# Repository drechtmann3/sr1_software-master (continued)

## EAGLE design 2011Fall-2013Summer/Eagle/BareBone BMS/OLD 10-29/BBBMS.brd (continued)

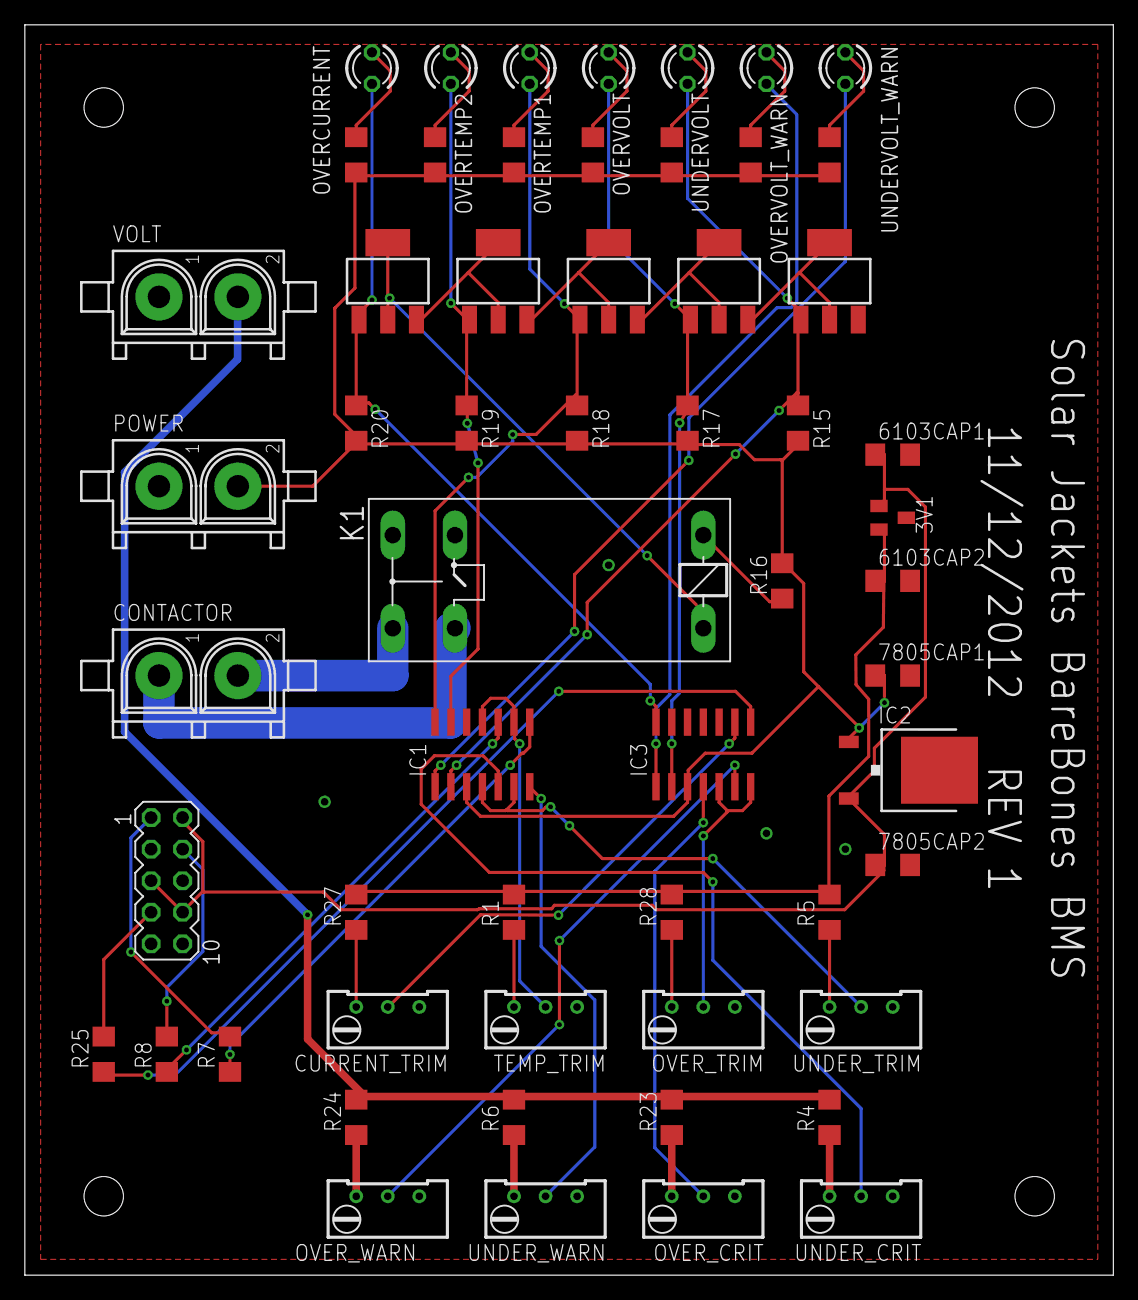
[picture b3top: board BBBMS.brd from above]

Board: 2 copper layers, 87.6 x 100.6 mm, 57 parts (0 on the bottom side), 49 nets.

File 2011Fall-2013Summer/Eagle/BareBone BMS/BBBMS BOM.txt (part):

Partlist exported from C:/Users/Reid Kersey/Documents/School/Solar Jackets/SubVersion/Eagle/BareBone BMS/BBBMS.sch at 11/14/2012 2:11:55 AM

Part            Value               Device              Package  Description                                                    MF                   MPN OC_FARNELL OC_NEWARK
3V1             MAX6103             MAX6103             SOT23                                                                                                                
6103CAP1        1uF                 C-USC0402           C0402    CAPACITOR, American symbol                                                                                  
6103CAP2        1uF                 C-USC0402           C0402    CAPACITOR, American symbol                                                                                  
7805CAP1        1uF                 C-USC0402           C0402    CAPACITOR, American symbol                                                                                  
7805CAP2        1uF                 C-USC0402           C0402    CAPACITOR, American symbol                                                                                  
CONTACTOR       350428-1            350428-1            350428-1 Universal MATE-N-LOK .250" Centerline, 600 V, 19 - 36 A max                                                 
CURRENT_TRIM    1k                  R-TRIMM64W          RTRIM64W Trimm resistor                                                                                              
IC1             LM339D              LM339D              SO14     Low Power Low Offset Voltage Quad Comparators                                                               
IC2             7805DT              7805DT              TO252    Positive VOLTAGE REGULATOR                                                                                  
IC3             LM339D              LM339D              SO14     Low Power Low Offset Voltage Quad Comparators                                                               
K1              G2REA               G2REA               G2REA    RELAY                                                                                   unknown    unknown  
OVERCURRENT     TLLG4400            TLLG4400            LED3MM   Low Current (2mA) LED 3 mm Tinted Diffused Package color GREEN VISHAY SEMICONDUCTOR     1612435             
OVERCURRENT_FET N-HEXFET-2D_SOT232- N-HEXFET-2D_SOT232- SOT223   HEXFET® Power MOSFET 2 Drain connects                                                                       
OVERTEMP1       TLLG4400            TLLG4400            LED3MM   Low Current (2mA) LED 3 mm Tinted Diffused Package color GREEN VISHAY SEMICONDUCTOR     1612435             
OVERTEMP1_FET   N-HEXFET-2D_SOT232- N-HEXFET-2D_SOT232- SOT223   HEXFET® Power MOSFET 2 Drain connects                                                                       
OVERTEMP2       TLLG4400            TLLG4400            LED3MM   Low Current (2mA) LED 3 mm Tinted Diffused Package color GREEN VISHAY SEMICONDUCTOR     1612435             
OVERTEMP2_FET   N-HEXFET-2D_SOT232- N-HEXFET-2D_SOT232- SOT223   HEXFET® Power MOSFET 2 Drain connects                                                                       
OVERVOLT        TLLG4400            TLLG4400            LED3MM   Low Current (2mA) LED 3 mm Tinted Diffused Package color GREEN VISHAY SEMICONDUCTOR     1612435             
OVERVOLT_FET    N-HEXFET-2D_SOT232- N-HEXFET-2D_SOT232- SOT223   HEXFET® Power MOSFET 2 Drain connects                                                                       
OVERVOLT_WARN   TLLG4400            TLLG4400            LED3MM   Low Current (2mA) LED 3 mm Tinted Diffused Package color GREEN VISHAY SEMICONDUCTOR     1612435             
OVER_CRIT       10k                 R-TRIMM64W          RTRIM64W Trimm resistor                                                                                              
OVER_TRIM       1k                  R-TRIMM64W          RTRIM64W Trimm resistor                                                                                              
OVER_WARN       10K                 R-TRIMM64W          RTRIM64W Trimm resistor                                                                                              
POWER           350428-1            350428-1            350428-1 Universal MATE-N-LOK .250" Centerline, 600 V, 19 - 36 A max                                                 
R1              100                 R-US_M1406          M1406    RESISTOR, American symbol                                                                                   
R4              100k                R-US_M1406          M1406    RESISTOR, American symbol                                                                                   
R5              100                 R-US_M1406          M1406    RESISTOR, American symbol                                                                                   
R6              100k                R-US_M1406          M1406    RESISTOR, American symbol                                                                                   
R7              100                 R-US_M1406          M1406    RESISTOR, American symbol                                                                                   
R8              100                 R-US_M1406          M1406    RESISTOR, American symbol                                                                                   
R9              1k                  R-US_M1406          M1406    RESISTOR, American symbol                                                                                   
R10             1k                  R-US_M1406          M1406    RESISTOR, American symbol                                                                                   
R13             1k                  R-US_M1406          M1406    RESISTOR, American symbol                                                                                   
R14             1k                  R-US_M1406          M1406    RESISTOR, American symbol                                                                                   
R15             1k                  R-US_M1406          M1406    RESISTOR, American symbol                                                                                   
R16             100                 R-US_M1406          M1406    RESISTOR, American symbol                                                                                   
R17             1k                  R-US_M1406          M1406    RESISTOR, American symbol                                                                                   
R18             1k                  R-US_M1406          M1406    RESISTOR, American symbol                                                                                   
R19             1k                  R-US_M1406          M1406    RESISTOR, American symbol                                                                                   
R20             1k                  R-US_M1406          M1406    RESISTOR, American symbol                                                                                   
R23             100k                R-US_M1406          M1406    RESISTOR, American symbol                                                                                   
R24             100k                R-US_M1406          M1406    RESISTOR, American symbol                                                                                   
R25             1k                  R-US_M1406          M1406    RESISTOR, American symbol                                                                                   
R27             100                 R-US_M1406          M1406    RESISTOR, American symbol                                                                                   
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
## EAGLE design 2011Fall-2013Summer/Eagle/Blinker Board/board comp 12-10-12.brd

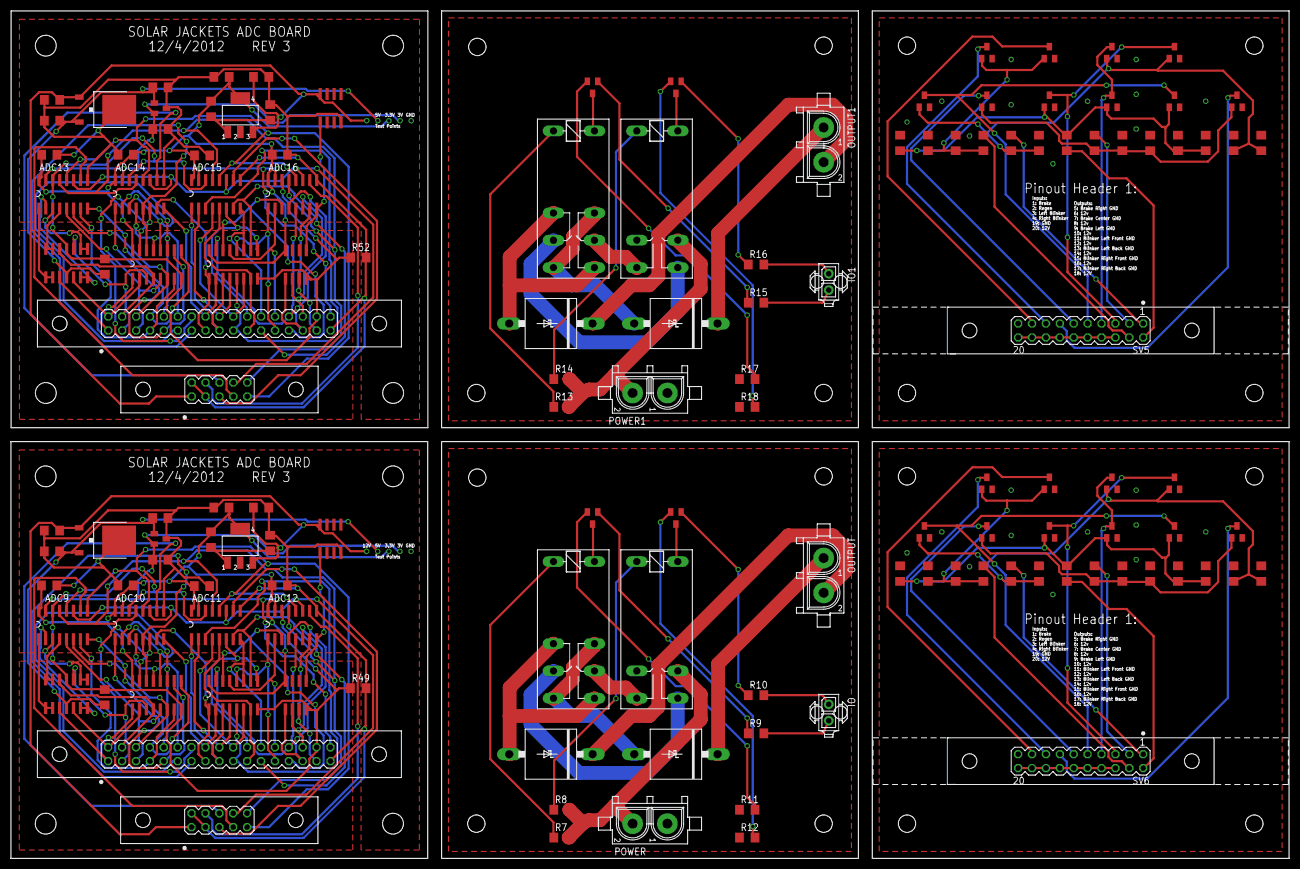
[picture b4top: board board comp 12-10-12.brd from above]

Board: 2 copper layers, 233.7 x 154.9 mm, 136 parts (0 on the bottom side), 170 nets.

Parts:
3V2, 3V3: MAX6103; SOT23
5V2, 5V3: LM7805TV; TO252
317CAP5, 317CAP7, 7805CAP6, 7805CAP8: .33uF; C1206
317CAP6, 317CAP8, 6103CAP5, 6103CAP6, 6103CAP7, 6103CAP8, 7805CAP5, 7805CAP7: 1uF; C1206
6484CAP3, 6484CAP4: .1uF; C1206
ADC9, ADC10, ADC11, ADC12, ADC13, ADC14, ADC15, ADC16: MCP-3008; SO16
ADC_CAP9, ADC_CAP10, ADC_CAP11, ADC_CAP12, ADC_CAP13, ADC_CAP14, ADC_CAP15, ADC_CAP16: .1uF; C1206
BLINKER-L1, BLINKER-L2, BLINKER-L3, BLINKER-L4: PMV56XN215; SOT23
BLINKER-R1, BLINKER-R2, BLINKER-R3, BLINKER-R4: PMV56XN215; SOT23
BRAKE-C1, BRAKE-C2, BRAKE-C3, BRAKE-C4: PMV56XN215; SOT23
BRAKE-L1, BRAKE-L2, BRAKE-L3, BRAKE-L4: PMV56XN215; SOT23
BRAKE-R1, BRAKE-R2, BRAKE-R3, BRAKE-R4: PMV56XN215; SOT23
D1, D2, D3, D4: 6A4; P6T15
IC3, IC4: LM317; SOT223
IO, IO1: 794681-2
K1, K3: G2R2
K2, K4: G2R2A
LMC6484_3, LMC6484_4: LMC6484; SO14
OUTPUT, OUTPUT1: 350428-1
POWER, POWER1: 350428-1
R7, R8, R9, R10, R13, R14, R15, R16, R19, R20, R21, R22, R23, R24, R25, R26, R27, R28, R29, R30, R31, R32, R33, R34, R35, R36, R37, R38, R39, R40, R41, R42, R43, R44, R45, R46: 1k; R1206
R11, R12, R17, R18, R49, R52: 0; R1206
R47, R50: 220; R1206
R48, R51: 361; R1206
SV5, SV6: AMPLATCH-20; MA10-2
SV7, SV9: MA17-2
SV8, SV10: MA05-2
T1, T2, T3, T4: PMV56XN; SOT23
U$9, U$10, U$13, U$14: SP720APP; SO16
U$11, U$15: SP721APP; SO-08
U$12, U$16: LM35; SO-08

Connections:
3.3V2: 317CAP6.1, ADC9.16, ADC10.16, ADC11.16, ADC12.16, ADC_CAP9.1, ADC_CAP10.1, ADC_CAP11.1, ADC_CAP12.1, IC3.4, R47.1, U$9.16, U$10.16, U$11.8
3.3V3: 317CAP8.1, ADC13.16, ADC14.16, ADC15.16, ADC16.16, ADC_CAP13.1, ADC_CAP14.1, ADC_CAP15.1, ADC_CAP16.1, IC4.4, R50.1, U$13.16, U$14.16, U$15.8
5V2: 3V2.1, 5V2.2, 6103CAP5.1, 6484CAP3.1, 7805CAP5.1, LMC6484_3.4
5V3: 3V3.1, 5V3.2, 6103CAP7.1, 6484CAP4.1, 7805CAP7.1, LMC6484_4.4
12V2: K2.P1, POWER.2, R7.2, R8.2
12V3: K4.P1, POWER1.2, R13.2, R14.2
12V4: SV5.6, SV5.8, SV5.10, SV5.12, SV5.14, SV5.16, SV5.18, SV5.20
12V5: SV6.6, SV6.8, SV6.10, SV6.12, SV6.14, SV6.16, SV6.18, SV6.20
12V6: 5V2.1, 317CAP5.1, 7805CAP6.1, IC3.3, SV8.1, U$12.8
12V7: 5V3.1, 317CAP7.1, 7805CAP8.1, IC4.3, SV10.1, U$16.8
A9: ADC9.1, LMC6484_3.1, LMC6484_3.2
A10: ADC9.2, LMC6484_3.6, LMC6484_3.7
A11: ADC9.3, LMC6484_3.8, LMC6484_3.9
A12: ADC9.4, LMC6484_3.13, LMC6484_3.14
A13: ADC13.1, LMC6484_4.1, LMC6484_4.2
A14: ADC13.2, LMC6484_4.6, LMC6484_4.7
A15: ADC13.3, LMC6484_4.8, LMC6484_4.9
A16: ADC13.4, LMC6484_4.13, LMC6484_4.14
AGND2: 6484CAP3.2, ADC9.14, ADC10.14, ADC11.14, ADC12.14, LMC6484_3.11, R49.1, SV7.32, U$9.8, U$10.8, U$11.4
AGND3: 6484CAP4.2, ADC13.14, ADC14.14, ADC15.14, ADC16.14, LMC6484_4.11, R52.1, SV9.32, U$13.8, U$14.8, U$15.4
BLINKER_L: BLINKER-L1.1, BLINKER-L2.1, R23.2, R24.2, R32.2
BLINKER_L1: BLINKER-L3.1, BLINKER-L4.1, R37.2, R38.2, R46.2
BLINKER_L_BACK_-: BLINKER-L2.3, SV5.13
BLINKER_L_BACK_-1: BLINKER-L4.3, SV6.13
BLINKER_L_FRONT_-: BLINKER-L1.3, SV5.11
BLINKER_L_FRONT_-1: BLINKER-L3.3, SV6.11
BLINKER_R: BLINKER-R1.1, BLINKER-R2.1, R25.2, R26.2, R29.1
BLINKER_R1: BLINKER-R3.1, BLINKER-R4.1, R39.2, R40.2, R43.1
BLINKER_R_BACK_-: BLINKER-R2.3, SV5.17
BLINKER_R_BACK_-1: BLINKER-R4.3, SV6.17
BLINKER_R_FRONT_-: BLINKER-R1.3, SV5.15
BLINKER_R_FRONT_-1: BLINKER-R3.3, SV6.15
BRAKE: BRAKE-C1.1, BRAKE-L1.1, BRAKE-R1.1, R19.2, R21.2, R27.2, R31.2
BRAKE1: BRAKE-C4.1, BRAKE-L4.1, BRAKE-R3.1, R33.2, R35.2, R41.2, R45.2
BRAKE_C_-: BRAKE-C1.3, BRAKE-C2.3, SV5.7
BRAKE_C_-1: BRAKE-C3.3, BRAKE-C4.3, SV6.7
BRAKE_L_-: BRAKE-L1.3, BRAKE-L2.3, SV5.9
BRAKE_L_-1: BRAKE-L3.3, BRAKE-L4.3, SV6.9
BRAKE_REGEN: BRAKE-C2.1, BRAKE-L2.1, BRAKE-R2.1, R20.2, R22.2, R28.2, R30.1
BRAKE_REGEN1: BRAKE-C3.1, BRAKE-L3.1, BRAKE-R4.1, R34.2, R36.2, R42.2, R44.1
BRAKE_R_-: BRAKE-R1.3, BRAKE-R2.3, SV5.5
BRAKE_R_-1: BRAKE-R3.3, BRAKE-R4.3, SV6.5
DIR: IO.2, R9.2
DIR1: IO1.2, R15.2
GND2: K2.P2, POWER.1, R11.1, R12.1
GND3: K4.P2, POWER1.1, R17.1, R18.1
GND4: BLINKER-L1.2, BLINKER-L2.2, BLINKER-R1.2, BLINKER-R2.2, BRAKE-C1.2, BRAKE-C2.2, BRAKE-L1.2, BRAKE-L2.2, BRAKE-R1.2, BRAKE-R2.2, R19.1, R20.1, R21.1, R22.1, R23.1, R24.1, R25.1, R26.1, R27.1, R28.1, SV5.19
GND5: BLINKER-L3.2, BLINKER-L4.2, BLINKER-R3.2, BLINKER-R4.2, BRAKE-C3.2, BRAKE-C4.2, BRAKE-L3.2, BRAKE-L4.2, BRAKE-R3.2, BRAKE-R4.2, R33.1, R34.1, R35.1, R36.1, R37.1, R38.1, R39.1, R40.1, R41.1, R42.1, SV6.19
GND6: 3V2.3, 5V2.3, 317CAP5.2, 317CAP6.2, 6103CAP5.2, 6103CAP6.2, 7805CAP5.2, 7805CAP6.2, ADC9.9, ADC10.9, ADC11.9, ADC12.9, ADC_CAP9.2, ADC_CAP10.2, ADC_CAP11.2, ADC_CAP12.2, R48.2, R49.2, SV7.33, SV8.2, SV8.3, U$12.4
GND7: 3V3.3, 5V3.3, 317CAP7.2, 317CAP8.2, 6103CAP7.2, 6103CAP8.2, 7805CAP7.2, 7805CAP8.2, ADC13.9, ADC14.9, ADC15.9, ADC16.9, ADC_CAP13.2, ADC_CAP14.2, ADC_CAP15.2, ADC_CAP16.2, R51.2, R52.2, SV9.33, SV10.2, SV10.3, U$16.4
IN65: LMC6484_3.3, SV7.1, U$9.1
IN66: LMC6484_3.5, SV7.2, U$9.2
IN67: LMC6484_3.10, SV7.3, U$9.3
IN68: LMC6484_3.12, SV7.4, U$9.4
IN69: ADC9.8, SV7.8, U$9.9
IN70: ADC9.7, SV7.7, U$9.7
IN71: ADC9.6, SV7.6, U$9.6
IN72: ADC9.5, SV7.5, U$9.5
IN73: ADC10.2, SV7.10, U$9.11
IN74: ADC10.1, SV7.9, U$9.10
IN75: ADC10.5, SV7.13, U$9.14
IN76: ADC10.6, SV7.14, U$9.15
IN77: ADC11.8, SV7.24, U$10.11
IN78: ADC11.7, SV7.23, U$10.10
IN79: ADC11.5, SV7.21, U$10.7
IN80: ADC11.6, SV7.22, U$10.9
IN81: ADC11.4, SV7.20, U$10.6
IN82: ADC11.3, SV7.19, U$10.5
IN83: ADC11.1, SV7.17, U$10.3
IN84: ADC11.2, SV7.18, U$10.4
IN85: ADC12.1, SV7.25, U$10.12
IN86: ADC12.2, SV7.26, U$10.13
IN87: ADC12.4, SV7.28, U$10.15
IN88: ADC12.3, SV7.27, U$10.14
IN89: ADC12.8, U$11.5, U$12.1
IN90: ADC12.7, SV7.31, U$11.3
IN91: ADC12.5, SV7.29, U$11.1
IN92: ADC12.6, SV7.30, U$11.2
IN93: ADC10.8, SV7.16, U$10.2
IN94: ADC10.7, SV7.15, U$10.1
IN95: ADC10.3, SV7.11, U$9.12
IN96: ADC10.4, SV7.12, U$9.13
IN97: LMC6484_4.3, SV9.1, U$13.1
IN98: LMC6484_4.5, SV9.2, U$13.2
IN99: LMC6484_4.10, SV9.3, U$13.3
IN100: LMC6484_4.12, SV9.4, U$13.4
IN101: ADC13.8, SV9.8, U$13.9
IN102: ADC13.7, SV9.7, U$13.7
IN103: ADC13.6, SV9.6, U$13.6
IN104: ADC13.5, SV9.5, U$13.5
IN105: ADC14.2, SV9.10, U$13.11
IN106: ADC14.1, SV9.9, U$13.10
IN107: ADC14.5, SV9.13, U$13.14
IN108: ADC14.6, SV9.14, U$13.15
IN109: ADC15.8, SV9.24, U$14.11
IN110: ADC15.7, SV9.23, U$14.10
IN111: ADC15.5, SV9.21, U$14.7
IN112: ADC15.6, SV9.22, U$14.9
IN113: ADC15.4, SV9.20, U$14.6
IN114: ADC15.3, SV9.19, U$14.5
IN115: ADC15.1, SV9.17, U$14.3
IN116: ADC15.2, SV9.18, U$14.4
IN117: ADC16.1, SV9.25, U$14.12
IN118: ADC16.2, SV9.26, U$14.13
IN119: ADC16.4, SV9.28, U$14.15
IN120: ADC16.3, SV9.27, U$14.14
IN121: ADC16.8, U$15.5, U$16.1
IN122: ADC16.7, SV9.31, U$15.3
IN123: ADC16.5, SV9.29, U$15.1
IN124: ADC16.6, SV9.30, U$15.2
IN125: ADC14.8, SV9.16, U$14.2
IN126: ADC14.7, SV9.15, U$14.1
IN127: ADC14.3, SV9.11, U$13.12
IN128: ADC14.4, SV9.12, U$13.13
MOTOR+: D2.C, OUTPUT.2
MOTOR+1: D4.C, OUTPUT1.2
MOTOR+_PRE: D2.A, K1.O2, K1.S1
MOTOR+_PRE1: D4.A, K3.O2, K3.S1
MOTOR-: D1.C, OUTPUT.1
MOTOR-1: D3.C, OUTPUT1.1
MOTOR-_PRE: D1.A, K1.O1, K1.S2
MOTOR-_PRE1: D3.A, K3.O1, K3.S2
unnamed: K1.P2, K2.S1
unnamed: K1.P1, K2.S2
unnamed: K1.1, R7.1
unnamed: K2.1, R8.1
unnamed: K1.2, T1.3
unnamed: K2.2, T2.3
unnamed: R10.1, T2.1
unnamed: R9.1, T1.1
unnamed: R11.2, T1.2
unnamed: R12.2, T2.2
unnamed: K3.P2, K4.S1
unnamed: K3.P1, K4.S2
unnamed: K3.1, R13.1
unnamed: K4.1, R14.1
unnamed: K3.2, T3.3
unnamed: K4.2, T4.3
unnamed: R16.1, T4.1
unnamed: R15.1, T3.1
unnamed: R17.2, T3.2
unnamed: R18.2, T4.2
unnamed: R30.2, SV5.2
unnamed: R29.2, SV5.4
unnamed: R31.1, SV5.1
unnamed: R32.1, SV5.3
unnamed: R44.2, SV6.2
unnamed: R43.2, SV6.4
unnamed: R45.1, SV6.1
unnamed: R46.1, SV6.3
unnamed: IC3.1, R47.2, R48.1
unnamed: IC4.1, R50.2, R51.1
ON: IO.1, R10.2
ON1: IO1.1, R16.2
SPI_CLK2: ADC9.13, ADC10.13, ADC11.13, ADC12.13, SV8.10
SPI_CLK3: ADC13.13, ADC14.13, ADC15.13, ADC16.13, SV10.10
SPI_CS9: ADC9.10, SV8.7
SPI_CS10: ADC10.10, SV8.6
SPI_CS11: ADC12.10, SV8.4
SPI_CS12: ADC11.10, SV8.5
SPI_CS13: ADC13.10, SV10.7
SPI_CS14: ADC14.10, SV10.6
SPI_CS15: ADC16.10, SV10.4
SPI_CS16: ADC15.10, SV10.5
SPI_DIN2: ADC9.11, ADC10.11, ADC11.11, ADC12.11, SV8.8
SPI_DIN3: ADC13.11, ADC14.11, ADC15.11, ADC16.11, SV10.8
SPI_DOUT2: ADC9.12, ADC10.12, ADC11.12, ADC12.12, SV8.9
SPI_DOUT3: ADC13.12, ADC14.12, ADC15.12, ADC16.12, SV10.9
VREF2: 3V2.2, 6103CAP6.1, ADC9.15, ADC10.15, ADC11.15, ADC12.15, SV7.34
VREF3: 3V3.2, 6103CAP8.1, ADC13.15, ADC14.15, ADC15.15, ADC16.15, SV9.34

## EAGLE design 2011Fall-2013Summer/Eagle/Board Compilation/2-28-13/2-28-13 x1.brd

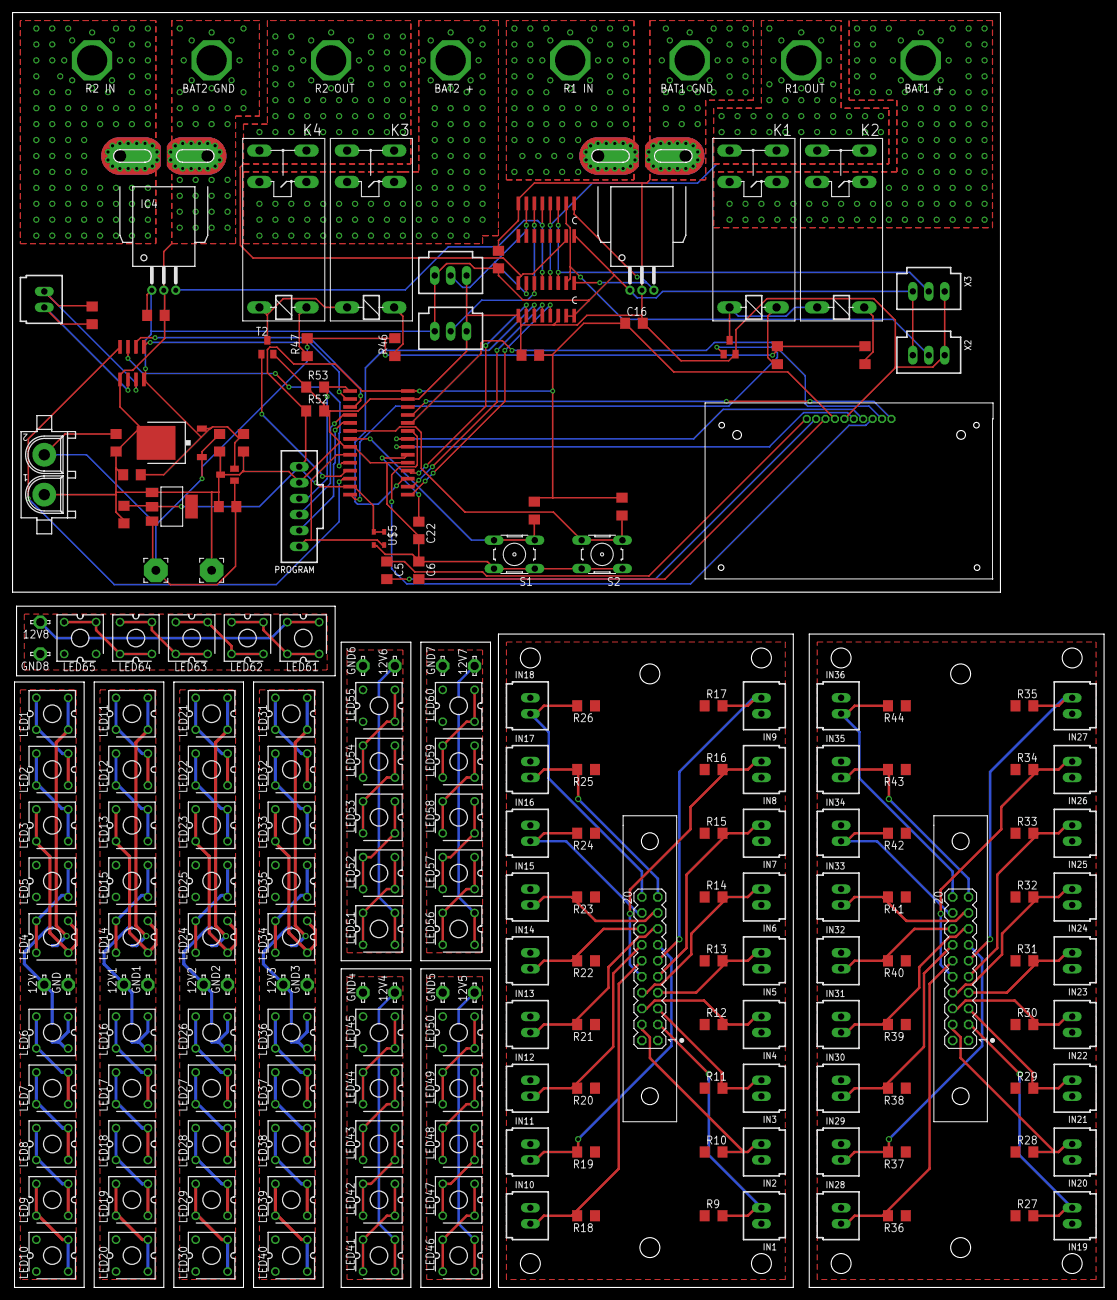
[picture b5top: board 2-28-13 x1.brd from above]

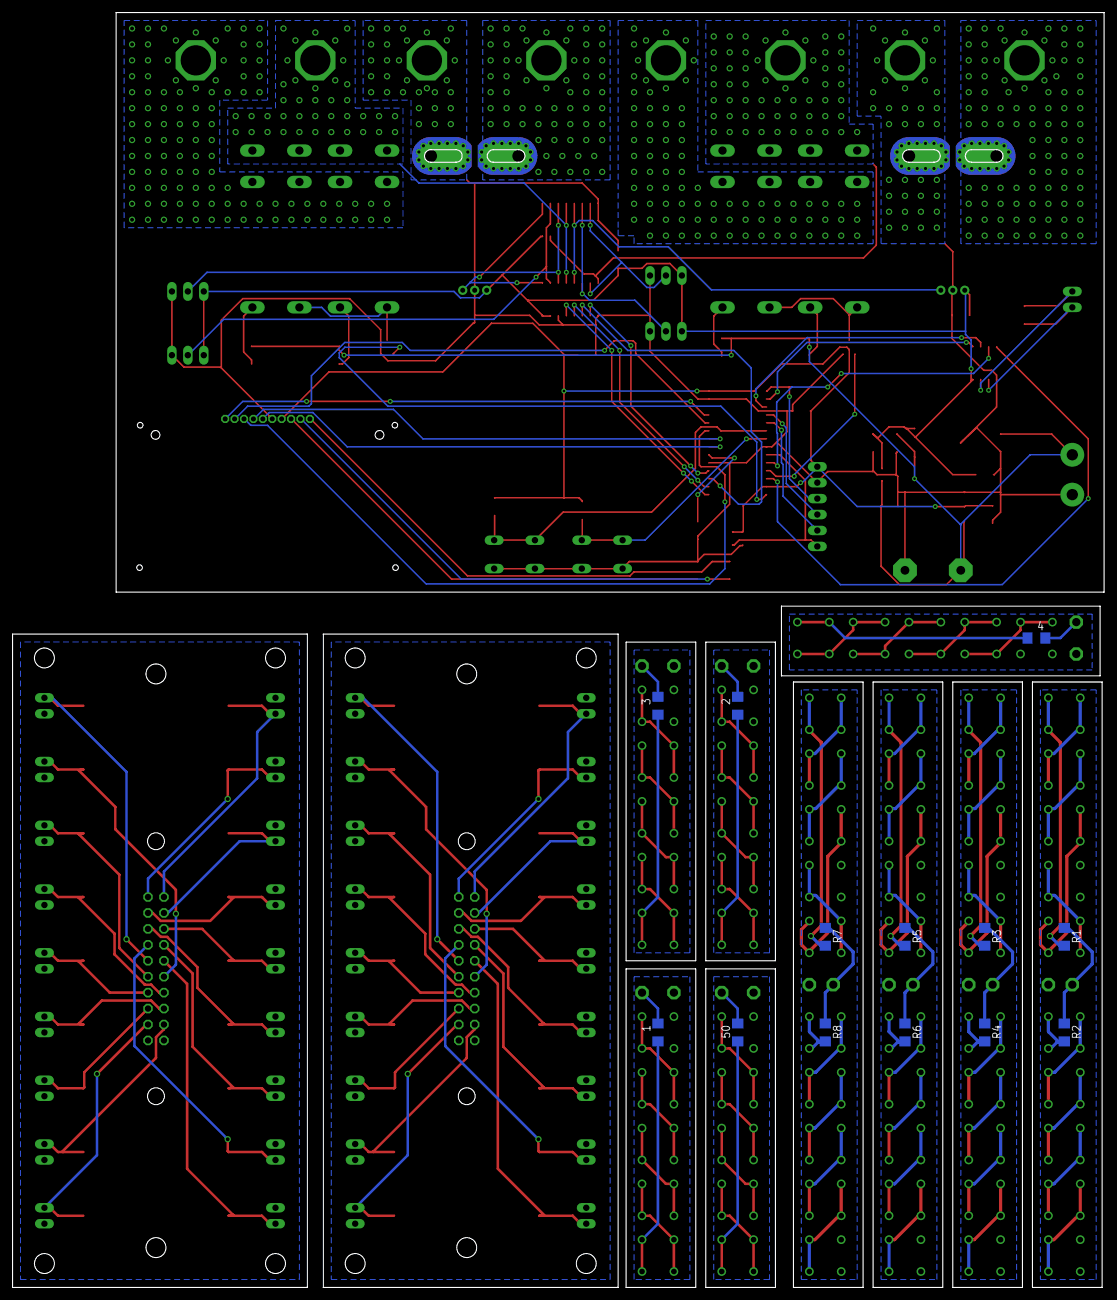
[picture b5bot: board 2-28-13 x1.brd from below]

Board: 2 copper layers, 174.0 x 203.2 mm, 228 parts (13 on the bottom side), 172 nets.

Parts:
1, 2, 3, 4, 50: RESISTORSMD1206; R1206
12V, 12V1, 12V2, 12V3, 12V4, 12V5, 12V6, 12V7, 12V8: LSP13
BAT+_1: BAT1 +; SOLDERPAD
BAT+_2: BAT2 +; SOLDERPAD
BAT-_1: BAT1 GND; SOLDERPAD
BAT-_2: BAT2 GND; SOLDERPAD
C1: .3uF; C1206
C2, C3, C4, C5, C6, C7, C8, C9, C10, C22: 1uF; C1206
C16, C48: .1uF; C1206
GND, GND1, GND2, GND3, GND4, GND5, GND6, GND7, GND8: LSP13
IC1: 7805DT; TO252
IC2, IC4: ACS758ECB-200B-PFF-T; CB-PFF
IC3: REG1117; SOT223
IN1, IN2, IN3, IN4, IN5, IN6, IN7, IN8, IN9, IN10, IN11, IN12, IN13, IN14, IN15, IN16, IN17, IN18, IN19, IN20, IN21, IN22, IN23, IN24, IN25, IN26, IN27, IN28, IN29, IN30, IN31, IN32, IN33, IN34, IN35, IN36: C-GRID-02-70543; 70543-02
J1: 350428-1
K1, K2, K3, K4: G2REA
LED1, LED11, LED21, LED31, LED41, LED46, LED51, LED56, LED61: LED1; CP41B
LED2, LED12, LED22, LED32, LED42, LED47, LED52, LED57, LED62: LED2; CP41B
LED3, LED13, LED23, LED33, LED43, LED48, LED53, LED58, LED63: LED3; CP41B
LED4, LED14, LED24, LED34, LED44, LED49, LED54, LED59, LED64: LED4; CP41B
LED5, LED15, LED25, LED35, LED45, LED50, LED55, LED60, LED65: LED5; CP41B
LED6, LED16, LED26, LED36: LED6; CP41B
LED7, LED17, LED27, LED37: LED7; CP41B
LED8, LED18, LED28, LED38: LED8; CP41B
LED9, LED19, LED29, LED39: LED9; CP41B
LED10, LED20, LED30, LED40: LED10; CP41B
PAD_12V: 12v; 3,81/1,4
PAD_GND: gnd; 3,81/1,4
PROGRAM: C-GRID-06-70543; 70543-06
R1, R2, R3, R4, R5, R6, R7, R8: 50; R1206
R9, R10, R11, R12, R13, R14, R15, R16, R17, R18, R19, R20, R21, R22, R23, R24, R25, R26, R27, R28, R29, R30, R31, R32, R33, R34, R35, R36, R37, R38, R39, R40, R41, R42, R43, R44, R45, R46, R47, R48, R49, R169: 1K; R1206
R50: 120; R1206
R52: 10k\; R1206
R53: 470; R1206
R_IN_1: R1 IN; SOLDERPAD
R_IN_2: R2 IN; SOLDERPAD
R_OUT_1: R1 OUT; SOLDERPAD
R_OUT_2: R2 OUT; SOLDERPAD
S1, S2: B3F-10XX
T1, T2: PMV56XN; SOT23
U$1, U$2: AMP_LATCH-20; MA10-2
U$3: MCP-3008; SO16
U$4: PIC24HJ128GP-202; SO28W
U$5: ASE
U$6: LCD_SCREEN
U$7: MAX6105; SOT23
U$8: SP720APP; SO16
U$9: MAX3440E; SO-08
X1: BAT2 TEMP 1; 70543-03
X2: BAT1 TEMP1; 70543-03
X3: BAT1 TEMP2; 70543-03
X4: BAT2 TEMP2; 70543-03
X5: rs-485; 70543-02

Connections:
3.3V: IN1.1, IN2.1, IN3.1, IN4.1, IN5.1, IN6.1, IN7.1, IN8.1, IN9.1, IN10.1, IN11.1, IN12.1, IN13.1, IN14.1, IN15.1, IN16.1, IN17.1, IN18.1, U$1.1
3.3V1: IN19.1, IN20.1, IN21.1, IN22.1, IN23.1, IN24.1, IN25.1, IN26.1, IN27.1, IN28.1, IN29.1, IN30.1, IN31.1, IN32.1, IN33.1, IN34.1, IN35.1, IN36.1, U$2.1
+3V3: C9.1, C16.1, C48.1, IC3.2, PROGRAM.6, R48.2, R49.1, R52.1, U$4.13, U$4.28, U$5.1, U$5.4, U$6.7
+5V: C3.2, C4.1, C7.1, C10.2, IC1.2, IC2.1, IC4.1, U$3.15, U$3.16, U$7.2, U$8.16, U$9.8, X1.3, X2.3, X3.3, X4.3
+12V: C1.1, C2.1, C8.1, IC1.1, IC3.3, J1.2, PAD_12V.1, R45.2, R46.2, R47.2, R169.2, U$7.1
CH0: IC2.3, U$3.1, U$8.1
CH1: U$3.2, U$8.2, X2.2
CH2: U$3.3, U$8.3, X3.2
CH3: K1.S, K1.S@, K2.S, K2.S@, R_OUT_1.P$1, U$3.4, U$8.4
CH4: IC4.3, U$3.5, U$8.5
CH5: U$3.6, U$8.6, X1.2
CH6: U$3.7, U$8.7, X4.2
CH7: K3.S, K3.S@, K4.S, K4.S@, R_OUT_2.P$1, U$3.8, U$8.15
GND: GND.MP, LED5.1, LED5.4, LED10.1, LED10.4
GND1: GND1.MP, LED15.1, LED15.4, LED20.1, LED20.4
GND2: GND2.MP, LED25.1, LED25.4, LED30.1, LED30.4
GND3: GND3.MP, LED35.1, LED35.4, LED40.1, LED40.4
GND4: GND4.MP, LED45.1, LED45.4
GND5: GND5.MP, LED50.1, LED50.4
GND6: GND6.MP, LED55.1, LED55.4
GND7: GND7.MP, LED60.1, LED60.4
GND8: GND8.MP, LED65.1, LED65.4
GND9: R9.1, R10.1, R11.1, R12.1, R13.1, R14.1, R15.1, R16.1, R17.1, R18.1, R19.1, R20.1, R21.1, R22.1, R23.1, R24.1, R25.1, R26.1, U$1.2
GND10: R27.1, R28.1, R29.1, R30.1, R31.1, R32.1, R33.1, R34.1, R35.1, R36.1, R37.1, R38.1, R39.1, R40.1, R41.1, R42.1, R43.1, R44.1, U$2.2
GND11: BAT-_1.P$1, BAT-_2.P$1, C1.2, C2.2, C3.1, C4.2, C6.1, C7.2, C8.2, C9.2, C10.1, C16.2, C22.2, C48.2, IC1.3, IC2.2, IC2.IP+, IC2.IP+@2, IC2.IP+@3, IC2.IP+@4, IC2.IP+@5, IC2.IP+@6, IC2.IP+@7, IC2.IP+@8, IC2.IP+@9, IC2.IP+@10, IC2.IP+@11, IC2.IP+@12, IC2.IP+@13, IC2.IP+@14, IC2.IP+@15, IC2.IP+@16, IC2.IP+@17, IC3.1, IC4.2, IC4.IP+, IC4.IP+@2, IC4.IP+@3, IC4.IP+@4, IC4.IP+@5, IC4.IP+@6, IC4.IP+@7, IC4.IP+@8, IC4.IP+@9, IC4.IP+@10, IC4.IP+@11, IC4.IP+@12, IC4.IP+@13, IC4.IP+@14, IC4.IP+@15, IC4.IP+@16, IC4.IP+@17, J1.1, PAD_GND.1, PROGRAM.5, R52.2, R53.1, S1.1, S1.2, S2.1, S2.2, T1.2, T2.2, U$3.9, U$3.14, U$4.8, U$4.19, U$4.27, U$5.2, U$6.6, U$7.3, U$8.8, U$9.5, X1.1, X2.1, X3.1, X4.1
IN1: IN1.2, R9.2, U$1.3
IN2: IN2.2, R10.2, U$1.4
IN3: IN3.2, R11.2, U$1.5
IN4: IN4.2, R12.2, U$1.6
IN5: IN5.2, R13.2, U$1.7
IN6: IN6.2, R14.2, U$1.8
IN7: IN7.2, R15.2, U$1.9
IN8: IN8.2, R16.2, U$1.10
IN9: IN9.2, R17.2, U$1.11
IN10: IN10.2, R18.2, U$1.12
IN11: IN11.2, R19.2, U$1.13
IN12: IN12.2, R20.2, U$1.14
IN13: IN13.2, R21.2, U$1.15
IN14: IN14.2, R22.2, U$1.16
IN15: IN15.2, R23.2, U$1.17
IN16: IN16.2, R24.2, U$1.18
IN17: IN17.2, R25.2, U$1.19
IN18: IN18.2, R26.2, U$1.20
IN19: IN19.2, R27.2, U$2.3
IN20: IN32.2, R40.2, U$2.16
IN21: IN33.2, R41.2, U$2.17
IN22: IN25.2, R33.2, U$2.9
IN23: IN29.2, R37.2, U$2.13
IN24: IN36.2, R44.2, U$2.20
IN25: IN34.2, R42.2, U$2.18
IN26: IN24.2, R32.2, U$2.8
IN27: IN23.2, R31.2, U$2.7
IN28: IN30.2, R38.2, U$2.14
IN29: IN31.2, R39.2, U$2.15
IN30: IN20.2, R28.2, U$2.4
IN31: IN21.2, R29.2, U$2.5
IN32: IN35.2, R43.2, U$2.19
IN33: IN28.2, R36.2, U$2.12
IN34: IN27.2, R35.2, U$2.11
IN35: IN26.2, R34.2, U$2.10
IN36: IN22.2, R30.2, U$2.6
MCLR: PROGRAM.4, R53.2, U$4.1
unnamed: LED1.2, LED1.3, R1.2
unnamed: LED1.1, LED1.4, LED2.2, LED2.3
unnamed: LED2.1, LED2.4, LED3.2, LED3.3
unnamed: LED3.1, LED3.4, LED4.2, LED4.3
unnamed: LED4.1, LED4.4, LED5.2, LED5.3
unnamed: LED6.2, LED6.3, R2.2
unnamed: LED6.1, LED6.4, LED7.2, LED7.3
unnamed: LED7.1, LED7.4, LED8.2, LED8.3
unnamed: 12V.MP, R1.1, R2.1
unnamed: LED8.1, LED8.4, LED9.2, LED9.3
unnamed: LED9.1, LED9.4, LED10.2, LED10.3
unnamed: LED11.2, LED11.3, R3.2
unnamed: LED11.1, LED11.4, LED12.2, LED12.3
unnamed: LED12.1, LED12.4, LED13.2, LED13.3
unnamed: LED13.1, LED13.4, LED14.2, LED14.3
unnamed: LED14.1, LED14.4, LED15.2, LED15.3
unnamed: 12V1.MP, R3.1, R4.1
unnamed: LED16.2, LED16.3, R4.2
unnamed: LED16.1, LED16.4, LED17.2, LED17.3
unnamed: LED17.1, LED17.4, LED18.2, LED18.3
unnamed: LED18.1, LED18.4, LED19.2, LED19.3
unnamed: LED19.1, LED19.4, LED20.2, LED20.3
unnamed: LED21.2, LED21.3, R5.2
unnamed: LED21.1, LED21.4, LED22.2, LED22.3
unnamed: LED22.1, LED22.4, LED23.2, LED23.3
unnamed: LED23.1, LED23.4, LED24.2, LED24.3
unnamed: LED24.1, LED24.4, LED25.2, LED25.3
unnamed: 12V2.MP, R5.1, R6.1
unnamed: LED26.2, LED26.3, R6.2
unnamed: LED26.1, LED26.4, LED27.2, LED27.3
unnamed: LED27.1, LED27.4, LED28.2, LED28.3
unnamed: LED28.1, LED28.4, LED29.2, LED29.3
unnamed: LED29.1, LED29.4, LED30.2, LED30.3
unnamed: LED31.2, LED31.3, R7.2
unnamed: LED31.1, LED31.4, LED32.2, LED32.3
unnamed: LED32.1, LED32.4, LED33.2, LED33.3
unnamed: LED33.1, LED33.4, LED34.2, LED34.3
unnamed: LED34.1, LED34.4, LED35.2, LED35.3
unnamed: 12V3.MP, R7.1, R8.1
unnamed: LED36.2, LED36.3, R8.2
unnamed: LED36.1, LED36.4, LED37.2, LED37.3
unnamed: LED37.1, LED37.4, LED38.2, LED38.3
unnamed: LED38.1, LED38.4, LED39.2, LED39.3
unnamed: LED39.1, LED39.4, LED40.2, LED40.3
unnamed: 50.2, LED41.2, LED41.3
unnamed: LED41.1, LED41.4, LED42.2, LED42.3
unnamed: LED42.1, LED42.4, LED43.2, LED43.3
unnamed: LED43.1, LED43.4, LED44.2, LED44.3
unnamed: LED44.1, LED44.4, LED45.2, LED45.3
unnamed: 12V4.MP, 50.1
unnamed: 1.2, LED46.2, LED46.3
unnamed: LED46.1, LED46.4, LED47.2, LED47.3
unnamed: LED47.1, LED47.4, LED48.2, LED48.3
unnamed: LED48.1, LED48.4, LED49.2, LED49.3
unnamed: LED49.1, LED49.4, LED50.2, LED50.3
unnamed: 1.1, 12V5.MP
unnamed: 2.2, LED51.2, LED51.3
unnamed: LED51.1, LED51.4, LED52.2, LED52.3
unnamed: LED52.1, LED52.4, LED53.2, LED53.3
unnamed: LED53.1, LED53.4, LED54.2, LED54.3
unnamed: LED54.1, LED54.4, LED55.2, LED55.3
unnamed: 2.1, 12V6.MP
unnamed: 3.2, LED56.2, LED56.3
unnamed: LED56.1, LED56.4, LED57.2, LED57.3
unnamed: LED57.1, LED57.4, LED58.2, LED58.3
unnamed: LED58.1, LED58.4, LED59.2, LED59.3
unnamed: LED59.1, LED59.4, LED60.2, LED60.3
unnamed: 3.1, 12V7.MP
unnamed: 4.2, LED61.2, LED61.3
unnamed: LED61.1, LED61.4, LED62.2, LED62.3
unnamed: LED62.1, LED62.4, LED63.2, LED63.3
unnamed: LED63.1, LED63.4, LED64.2, LED64.3
unnamed: LED64.1, LED64.4, LED65.2, LED65.3
unnamed: 4.1, 12V8.MP
unnamed: C22.1, U$4.20
unnamed: IC2.IP-, IC2.IP-@2, IC2.IP-@3, IC2.IP-@4, IC2.IP-@5, IC2.IP-@6, IC2.IP-@7, IC2.IP-@8, IC2.IP-@9, IC2.IP-@10, IC2.IP-@11, IC2.IP-@12, IC2.IP-@13, IC2.IP-@14, IC2.IP-@15, IC2.IP-@16, IC2.IP-@17, R_IN_1.P$1
unnamed: C6.2, U$6.8
unnamed: C5.2, U$6.9
unnamed: C5.1, U$6.10
unnamed: K1.2, K2.2, T1.3
unnamed: K2.1, R45.1
unnamed: BAT+_2.P$1, K3.P, K3.P@, K4.P, K4.P@
unnamed: K3.1, R46.1
unnamed: K3.2, K4.2, T2.3
unnamed: K4.1, R47.1
unnamed: IC4.IP-, IC4.IP-@2, IC4.IP-@3, IC4.IP-@4, IC4.IP-@5, IC4.IP-@6, IC4.IP-@7, IC4.IP-@8, IC4.IP-@9, IC4.IP-@10, IC4.IP-@11, IC4.IP-@12, IC4.IP-@13, IC4.IP-@14, IC4.IP-@15, IC4.IP-@16, IC4.IP-@17, R_IN_2.P$1
unnamed: K1.1, R169.1
unnamed: R50.2, U$9.7, X5.1
unnamed: R50.1, U$9.6, X5.2
unnamed: BAT+_1.P$1, K1.P, K1.P@, K2.P, K2.P@
OSC1: PROGRAM.1, U$4.9, U$5.3
PGEC1: PROGRAM.2, U$4.5
PGED1: PROGRAM.3, U$4.4
RA0: U$4.2, U$9.1
RA1: U$4.3, U$9.2
RA3: U$4.10, U$9.3
RA4: U$4.12, U$9.4
RB2: R49.2, S2.3, S2.4, U$4.6
RB3: R48.1, S1.3, S1.4, U$4.7
RB4: T2.1, U$4.11
RB5: T1.1, U$4.14
RB6: U$3.13, U$4.15
RB7: U$3.12, U$4.16
RB8: U$3.11, U$4.17
RB9: U$3.10, U$4.18
RB10: U$4.21, U$6.5
RB11: U$4.22, U$6.4
RB12: U$4.23, U$6.3
RB13: U$4.24, U$6.2
RB14: U$4.25, U$6.1
